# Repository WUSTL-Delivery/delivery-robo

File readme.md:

# Delivery Robotics

Delivery MonoRepo for robotics

- `ros2_ws/` — the robot's ROS 2 Jazzy workspace. Install its dependencies with
  `deployment/install_deps.sh`; see `deployment/README.md`. The Gazebo simulation lives in the
  `delivery-autonomy` submodule (`master_launch.py mode:=autonomy sim:=true`).
- `docker/` — the same environment as a container: a dev container for laptops and the runtime
  image the Pi can run instead of the native install; see `docker/README.md`.

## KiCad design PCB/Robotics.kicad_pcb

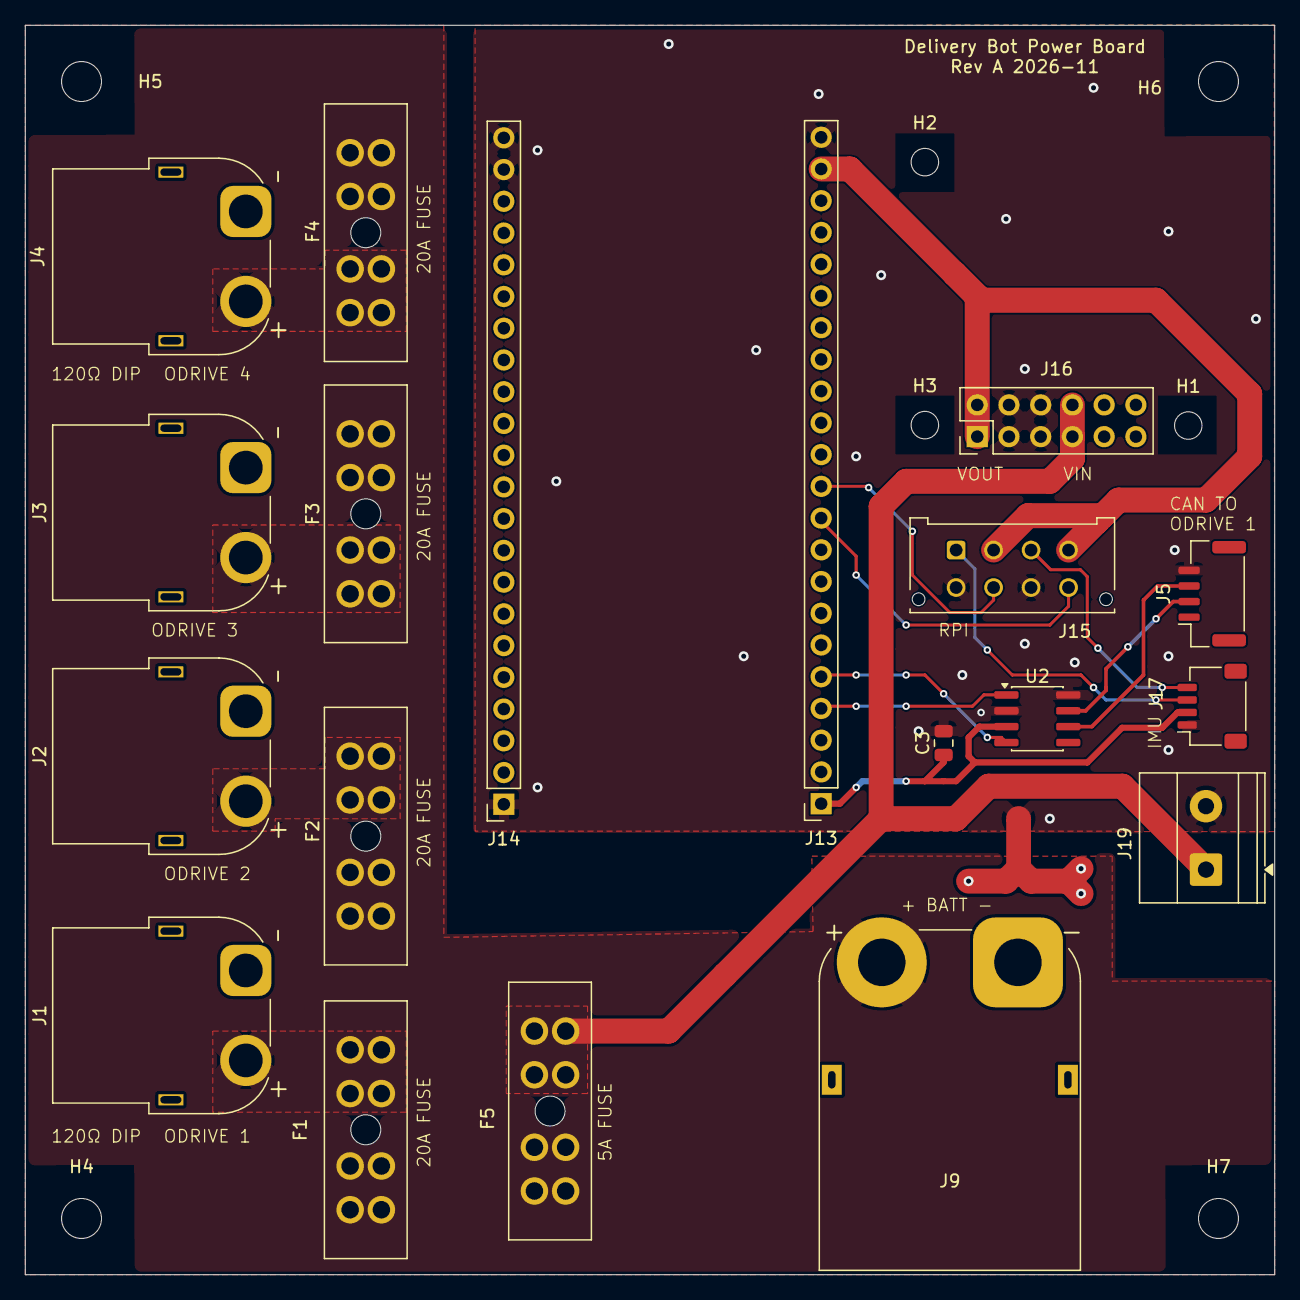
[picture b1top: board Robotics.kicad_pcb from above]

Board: 2 copper layers, 100.0 x 100.0 mm, 27 parts (0 on the bottom side), 18 nets.

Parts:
C3: 0.1µF 50V X7R; C_0805_2012Metric
F1, F2, F3, F4: 20A ATO; FuseHolder_Blade_ATO_Littelfuse_FLR_178.6165
F5: 5A ATO; FuseHolder_Blade_ATO_Littelfuse_FLR_178.6165
H1, H2, H3: M2 hole; MountingHole_2.2mm_M2
H4, H5, H6, H7: M3 hole; MountingHole_3.2mm_M3
J1, J2, J3, J4: XT60PW-F; AMASS_XT60PW-F_1x02_P7.20mm_Horizontal
J5: JST-GH 4P; JST_GH_SM04B-GHS-TB_1x04-1MP_P1.25mm_Horizontal
J9: XT90PW-M; AMASS_XT90PW-M_1x02_P10.90mm_Horizontal
J13, J14: 1x22 female 2.54mm; PinSocket_1x22_P2.54mm_Vertical
J15: Micro-Fit 2x4; Molex_Micro-Fit_3.0_43045-0812_2x04_P3.00mm_Vertical
J16: D36V50F5; PinHeader_2x06_P2.54mm_Vertical
J17: JST-SH 4P; JST_SH_SM04B-SRSS-TB_1x04-1MP_P1.00mm_Horizontal
J19: AUX REG OUT; TerminalBlock_Phoenix_MKDS-1,5-2-5.08_1x02_P5.08mm_Horizont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
NT1: NetTie; NetTie-2_SMD_Pad2.0mm
U2: SN65HVD230; SOIC-8_3.9x4.9mm_P1.27mm

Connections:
+3.3V: C3.1, J13.1, J17.2, U2.3 (VCC)
+5V: J13.21, J15.2, J15.4, J16.1, J16.2
/5V Logic and Sensors/CAN_RX: J13.5, U2.4 (R)
/5V Logic and Sensors/CAN_TX: J13.4, U2.1 (D)
/5V Logic and Sensors/ESP_RX_PI_TX: J13.11, J15.6
/5V Logic and Sensors/ESP_TX_PI_RX: J13.10, J15.8
/5V Logic and Sensors/PI_SCL: J15.3, J17.4
/5V Logic and Sensors/PI_SDA: J15.1, J17.3
/5V Logic and Sensors/VBAT_LOGIC: F5.2, J16.7, J16.8, J19.1
/Motor Distribution/CAN_H: J5.2, U2.7 (CANH)
/Motor Distribution/CAN_L: J5.3, U2.6 (CANL)
/Motor Distribution/GND_PWR: J1.1, J2.1, J3.1, J4.1, J9.1, NT1.1
/Motor Distribution/VBAT_MOTOR: F1.2, F2.2, F3.2, F4.2, F5.1, J9.2
/Motor Distribution/VM1: F1.1, J1.2
/Motor Distribution/VM2: F2.1, J2.2
/Motor Distribution/VM3: F3.1, J3.2
/Motor Distribution/VM4: F4.1, J4.2
GND: C3.2, J5.4, J13.22, J14.1, J14.21, J14.22, J15.5, J15.7, J16.3, J16.4, J16.5, J16.6, J17.1, J19.2, NT1.2, U2.2 (GND), U2.8 (Rs)
